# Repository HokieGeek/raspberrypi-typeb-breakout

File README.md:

# raspberrypi-typeb-breakout

[Reference page](http://www.raspberry-projects.com/pi/pi-hardware/raspberry-pi-model-b/model-b-io-pins)

One of these two is mine...

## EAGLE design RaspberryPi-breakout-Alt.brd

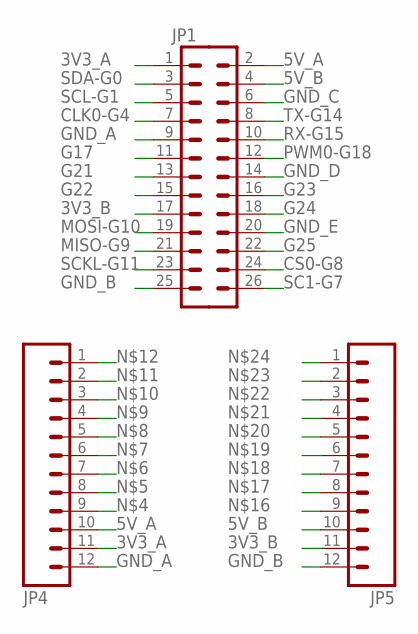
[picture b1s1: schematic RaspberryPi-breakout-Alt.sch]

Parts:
JP1: M13X22X13; 2X13
JP4, JP5: M12PTH; 1X12

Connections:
3V3_A: JP1.1, JP4.11
3V3_B: JP1.17, JP5.11
5V_A: JP1.2, JP4.10
5V_B: JP1.4, JP5.10
CLK0-G4: JP1.7
CS0-G8: JP1.24
G17: JP1.11
G21: JP1.13
G22: JP1.15
G23: JP1.16
G24: JP1.18
G25: JP1.22
GND_A: JP1.9, JP4.12
GND_B: JP1.25, JP5.12
GND_C: JP1.6
GND_D: JP1.14
GND_E: JP1.20
MISO-G9: JP1.21
MOSI-G10: JP1.19
PWM0-G18: JP1.12
RX-G15: JP1.10
SC1-G7: JP1.26
SCKL-G11: JP1.23
SCL-G1: JP1.5
SDA-G0: JP1.3
TX-G14: JP1.8

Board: 2 copper layers, 3 parts (0 on the bottom side), 6 nets, no tracks yet.

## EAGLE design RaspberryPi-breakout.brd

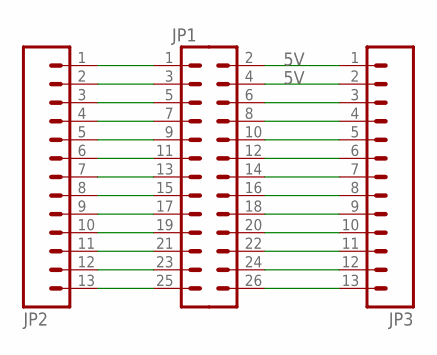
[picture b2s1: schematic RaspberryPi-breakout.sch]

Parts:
JP1: M13X22X13; 2X13
JP2, JP3: M13; 1X13

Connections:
unnamed: JP1.2, JP3.1
unnamed: JP1.4, JP3.2
unnamed: JP1.6, JP3.3
unnamed: JP1.8, JP3.4
unnamed: JP1.10, JP3.5
unnamed: JP1.12, JP3.6
unnamed: JP1.14, JP3.7
unnamed: JP1.16, JP3.8
unnamed: JP1.18, JP3.9
unnamed: JP1.20, JP3.10
unnamed: JP1.22, JP3.11
unnamed: JP1.24, JP3.12
unnamed: JP1.26, JP3.13
unnamed: JP1.25, JP2.13
unnamed: JP1.23, JP2.12
unnamed: JP1.21, JP2.11
unnamed: JP1.19, JP2.10
unnamed: JP1.17, JP2.9
unnamed: JP1.15, JP2.8
unnamed: JP1.13, JP2.7
unnamed: JP1.11, JP2.6
unnamed: JP1.9, JP2.5
unnamed: JP1.7, JP2.4
unnamed: JP1.5, JP2.3
unnamed: JP1.3, JP2.2
unnamed: JP1.1, JP2.1

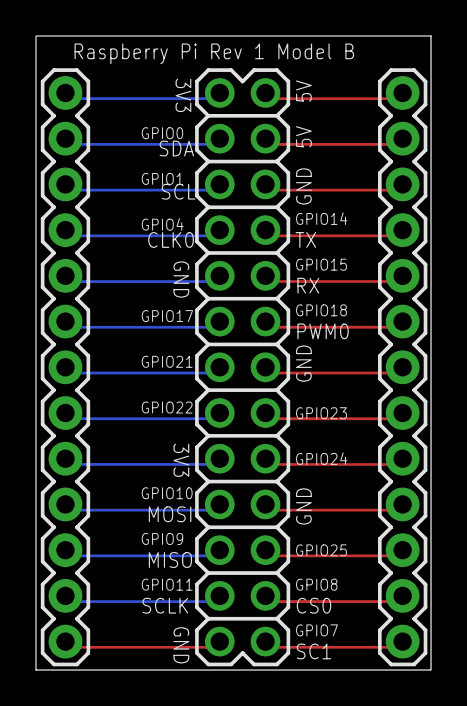
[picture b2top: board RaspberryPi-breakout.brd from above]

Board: 2 copper layers, 21.9 x 35.2 mm, 3 parts (0 on the bottom side), 26 nets.

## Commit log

2015-11-19 Adding the pinout links
2015-11-19 Pass #1
2015-11-19 Fleshed out some of the pins
2015-11-21 Created a new board
2015-11-21 Ignoring the lock files with new version of Eagle
2015-11-21 Trying to figure out this board

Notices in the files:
parts and their libraries:
SparkFun-Connectors: Licensing: Creative Commons ShareAlike 4.0 International - https://creativecommons.org/licenses/by-sa/4.0
